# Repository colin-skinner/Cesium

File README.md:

# Cesium
Library for all code related to development of my home server and space projects. 

The main goal of this project is not simply to learn, but to focus on following through and finishing each sprint. Additionally, with working prototypes and code, I plan to use my designs to help aspiring engineers who want to develop these skills as well (open-source, potentially?).

Each stage will act as a sort of version that had a fully working system. When I add changes that completely break a system, then I'll re-rev the design for a new version.

## Stage/Version 0 (Test Boards to get my footing)
* Rocket Project Test Rocket Backup Board (in case Avionics wants to fly another)
* ESP32 WROOM breakout with USB-UART communication, power circuit (3V3, 5V LDOs, Battery), and CAN Bus
* Breakout with sensors over I2C
* Breakout with sensors over SPI

## Stage/Version 1
The goal of this design is to create an assortment of avionics boards useful for ground testing of amateur rocketry or satellites using the CAN bus and various ADCs for data collection.

* ESP-32 Boards connected by CAN (for simplicity) 
  * CAN Transceiver - _MCP2562_ or _MCP2544FD_
* Boards designed to be small footprint and scaleable
    * Single function (i.e. Ducers, Load Cells, etc.)
* EGSE Board connects to server via D+/D- USB OTG (ESP32 S3 capability)
    * Future boards use _CP2102_ for USB-UART communication 
        * (ESP32 modules with ethernet do not have USB OTG)
* Telemetry
    * At this stage, unique codes for each telemetry
        * Based on CAN 11-bit arbitration ID for a maximum of 2048 different telemetries
    * EGSE board will act as the "router" between "support rack" and CAN bus boards
* List of Boards
    * Load Switches
        * FET switching, _INA180_ current sense, actuation feedback
        * Uses _ADS8688_ (optimized for single-ended signals)
    * Pressure Transducers
        * Uses _ADS8688_ (optimized for single-ended signals)
    * Load Cells
        * Uses _ADS1256_ (optimized for diffrential signals)
    * Flight Computer
        * SPI communication with IMU, GPS, and Altimeter  
    * Recovery board
        * Powering, arming, and receiving data from spare [Stratologger CF](http://www.perfectflite.com/SLCF.html) altimeter from my freshman year rocket class
    * EGSE/Power board
        * Routes CAN packets over USB to "support rack"
        * Commands from Python commander are sent to CAN bus
        
* GSE functionality (Python)
    * Commander (PyComm)
    * Telemetry visualization (Telem)

## Stage 2+
* ESP32 boards with wired Ethernet
    * PHY - _LAN8720AI_
    * Potential onboard switch - _KSZ8567S_
    * Separate VLAN to differentiate boards from home network
* Radio board for wireless communication
* Fully realize a proper home server/network diagram and organization
    * Firewall, different VLANs for things
    * Plex media server
    * My own local version of services called S-Suite (after G-Suite)
* GSE functionality (Python)
    * Real time DAQ (FizzVizz)
    * MySQL Integration for data storage
* Other software
    * Scheduler 
    * State Machine

## Other future ideas
* IOT Home Automation 
* Connecting my Octoprint 3D printers

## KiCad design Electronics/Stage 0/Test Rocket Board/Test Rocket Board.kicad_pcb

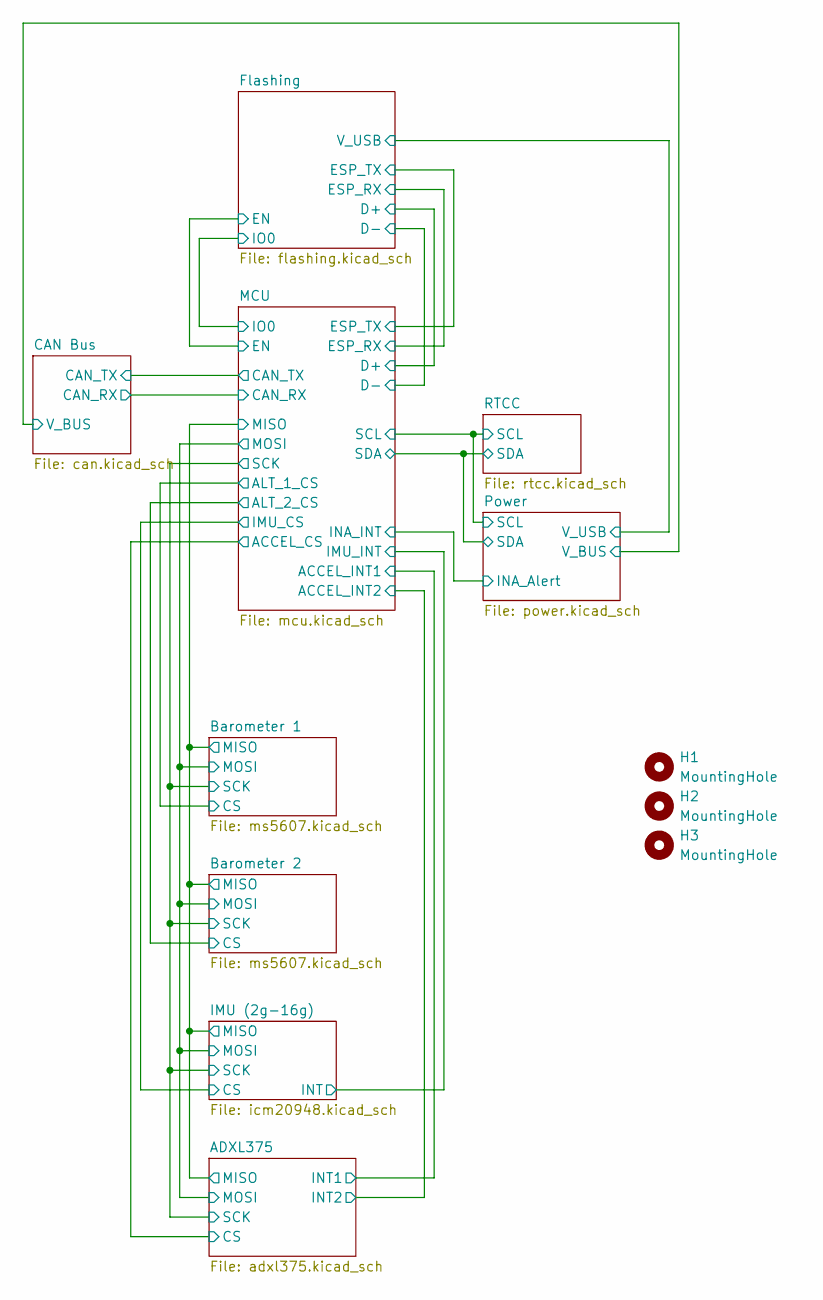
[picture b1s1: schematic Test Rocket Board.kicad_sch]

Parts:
H1, H2, H3: MountingHole; MountingHole_3.2mm_M3

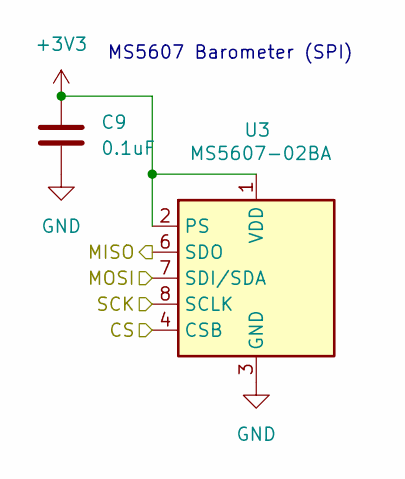
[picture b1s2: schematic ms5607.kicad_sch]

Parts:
C9: 0.1uF; C_0603_1608Metric
U3: MS5607-02BA; LGA-8_3x5mm_P1.25mm

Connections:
+3V3: C9.1, U3.1 (VDD), U3.2 (PS); also elsewhere on the board
/ADXL375/MISO: U3.6 (SDO); also elsewhere on the board
/ADXL375/MOSI: U3.7 (SDI/SDA); also elsewhere on the board
/ADXL375/SCK: U3.8 (SCLK); also elsewhere on the board
/Barometer 1/CS: U3.4 (CSB), U3.5 (CSB); also elsewhere on the board
GND: C9.2, U3.3 (GND); also elsewhere on the board

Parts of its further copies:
C10: 0.1uF; C_0603_1608Metric
U4: MS5607-02BA; LGA-8_3x5mm_P1.25mm

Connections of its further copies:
+3V3: C10.1, U4.1 (VDD), U4.2 (PS); also elsewhere on the board
/ADXL375/MISO: U4.6 (SDO); also elsewhere on the board
/ADXL375/MOSI: U4.7 (SDI/SDA); also elsewhere on the board
/ADXL375/SCK: U4.8 (SCLK); also elsewhere on the board
/Barometer 2/CS: U4.4 (CSB), U4.5 (CSB); also elsewhere on the board
GND: C10.2, U4.3 (GND); also elsewhere on the board

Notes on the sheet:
MS5607 Barometer (SPI)

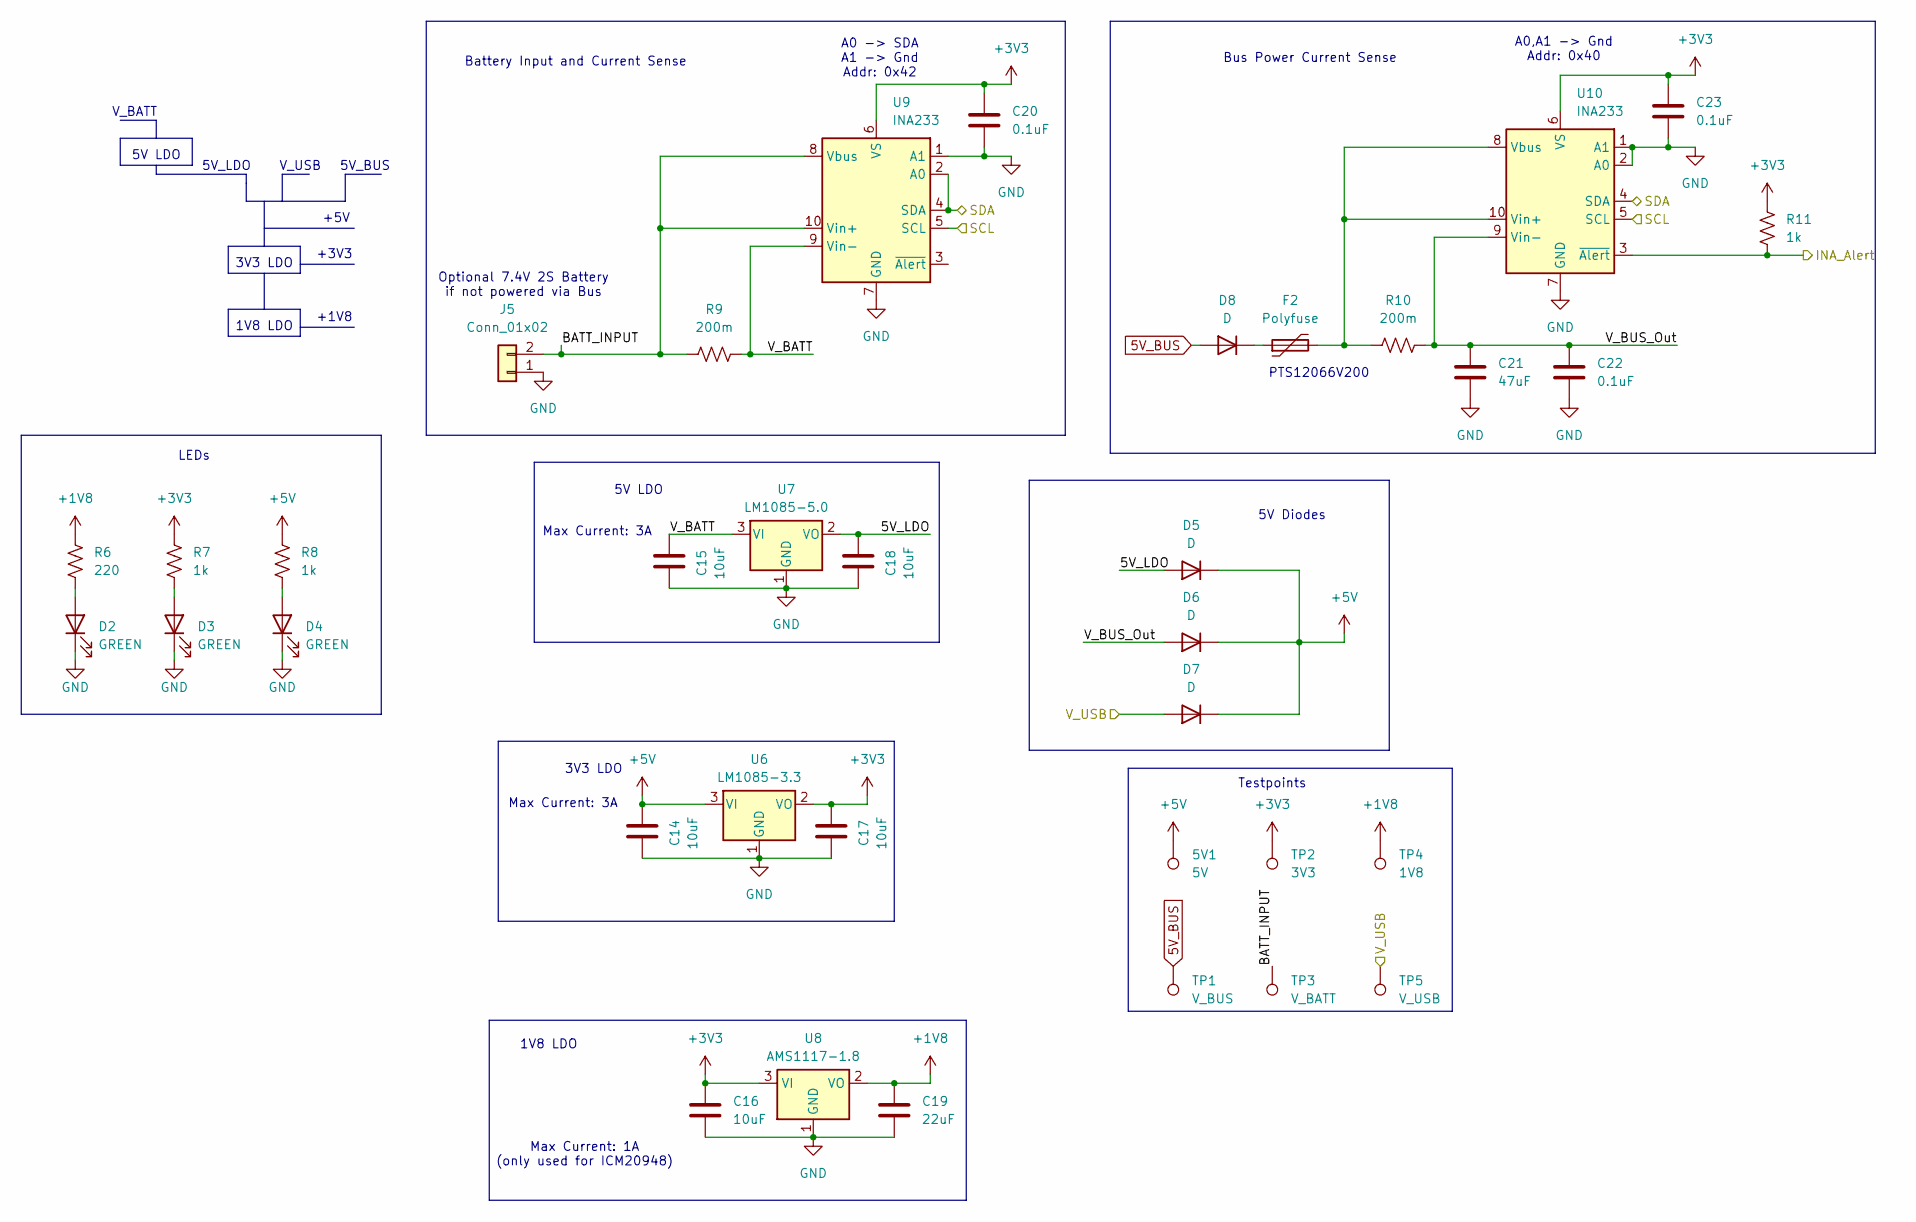
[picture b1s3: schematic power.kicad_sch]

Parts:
5V1: 5V; PinHeader_1x01_P2.54mm_Vertical
C14, C15, C16, C17, C18: 10uF; C_0603_1608Metric
C19: 22uF; C_0603_1608Metric
C20, C22, C23: 0.1uF; C_0603_1608Metric
C21: 47uF; C_0603_1608Metric
D2, D3, D4: GREEN; LED_0603_1608Metric_Pad1.05x0.95mm_HandSolder
D5, D6, D7, D8: D; D_0603_1608Metric
F2: Polyfuse; Fuse_1206_3216Metric
J5: Conn_01x02; AMASS_XT60-M_1x02_P7.20mm_Vertical
R6: 220; R_0603_1608Metric
R7, R8, R11: 1k; R_0603_1608Metric
R9, R10: 200m; R_0603_1608Metric
TP1: V_BUS; PinHeader_1x01_P2.54mm_Vertical
TP2: 3V3; PinHeader_1x01_P2.54mm_Vertical
TP3: V_BATT; PinHeader_1x01_P2.54mm_Vertical
TP4: 1V8; PinHeader_1x01_P2.54mm_Vertical
TP5: V_USB; PinHeader_1x01_P2.54mm_Vertical
U6: LM1085-3.3; TO-263-3_TabPin2
U7: LM1085-5.0; TO-263-3_TabPin2
U8: AMS1117-1.8; SOT-223-3_TabPin2
U9, U10: INA233; VSSOP-10_3x3mm_P0.5mm

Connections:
5V_BUS: D8.2 (A), TP1.1; also elsewhere on the board
+1V8: C19.1, R6.2, TP4.1, U8.2 (VO); also elsewhere on the board
+3V3: C16.1, C17.2, C20.1, C23.1, R7.2, R11.2, TP2.1, U6.2 (VO), U8.3 (VI), U9.6 (VS), U10.6 (VS); also elsewhere on the board
+5V: 5V1.1, C14.2, D5.1 (K), D6.1 (K), D7.1 (K), R8.2, U6.3 (VI); also elsewhere on the board
/Flashing/V_USB: D7.2 (A), TP5.1; also elsewhere on the board
/MCU/INA_INT: R11.1, U10.3 (~Alert); also elsewhere on the board
/MCU/SCL: U9.5 (SCL), U10.5 (SCL); also elsewhere on the board
/MCU/SDA: U9.2 (A0), U9.4 (SDA), U10.4 (SDA); also elsewhere on the board
/Power/5V_LDO: C18.2, D5.2 (A), U7.2 (VO)
/Power/BATT_INPUT: J5.2, R9.1, TP3.1, U9.8 (Vbus), U9.10 (Vin+)
/Power/V_BATT: C15.2, R9.2, U7.3 (VI), U9.9 (Vin-)
/Power/V_BUS_Out: C21.1, C22.1, D6.2 (A), R10.2, U10.9 (Vin-)
GND: C14.1, C15.1, C16.2, C17.1, C18.1, C19.2, C20.2, C21.2, C22.2, C23.2, D2.1 (K), D3.1 (K), D4.1 (K), J5.1, U6.1 (GND), U7.1 (GND), U8.1 (GND), U9.1 (A1), U9.7 (GND), U10.1 (A1), U10.2 (A0), U10.7 (GND); also elsewhere on the board
unnamed: D2.2 (A), R6.1
unnamed: D3.2 (A), R7.1
unnamed: D4.2 (A), R8.1
unnamed: D8.1 (K), F2.1
unnamed: F2.2, R10.1, U10.8 (Vbus), U10.10 (Vin+)

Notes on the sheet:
Battery Input and Current Sense
Testpoints
PTS12066V200
5V LDO
Max Current: 3A
LEDs
3V3 LDO
+3V3
Max Current: 1A (only used for ICM20948)
5V_LDO
1V8 LDO
Bus Power Current Sense
A0 -> SDA A1 -> Gnd Addr: 0x42
+1V8
+5V
5V_BUS
V_USB
Optional 7.4V 2S Battery if not powered via Bus
V_BATT
5V Diodes
A0,A1 -> Gnd Addr: 0x40

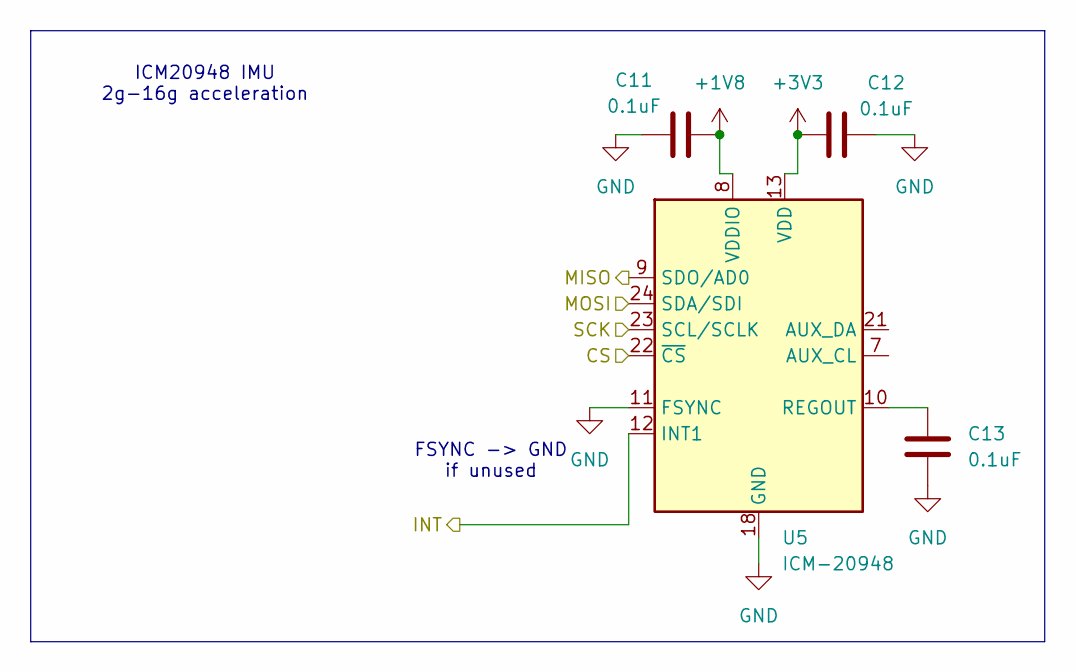
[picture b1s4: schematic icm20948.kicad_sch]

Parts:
C11, C12, C13: 0.1uF; C_0603_1608Metric
U5: ICM-20948; InvenSense_QFN-24_3x3mm_P0.4mm

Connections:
+1V8: C11.2, U5.8 (VDDIO); also elsewhere on the board
+3V3: C12.1, U5.13 (VDD); also elsewhere on the board
/ADXL375/MISO: U5.9 (SDO/AD0); also elsewhere on the board
/ADXL375/MOSI: U5.24 (SDA/SDI); also elsewhere on the board
/ADXL375/SCK: U5.23 (SCL/SCLK); also elsewhere on the board
/IMU (2g-16g)/CS: U5.22 (~CS); also elsewhere on the board
/IMU (2g-16g)/INT: U5.12 (INT1); also elsewhere on the board
GND: C11.1, C12.2, C13.2, U5.11 (FSYNC), U5.18 (GND), U5.20 (GND); also elsewhere on the board
unnamed: C13.1, U5.10 (REGOUT)

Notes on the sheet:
ICM20948 IMU 2g-16g acceleration
FSYNC -> GND if unused

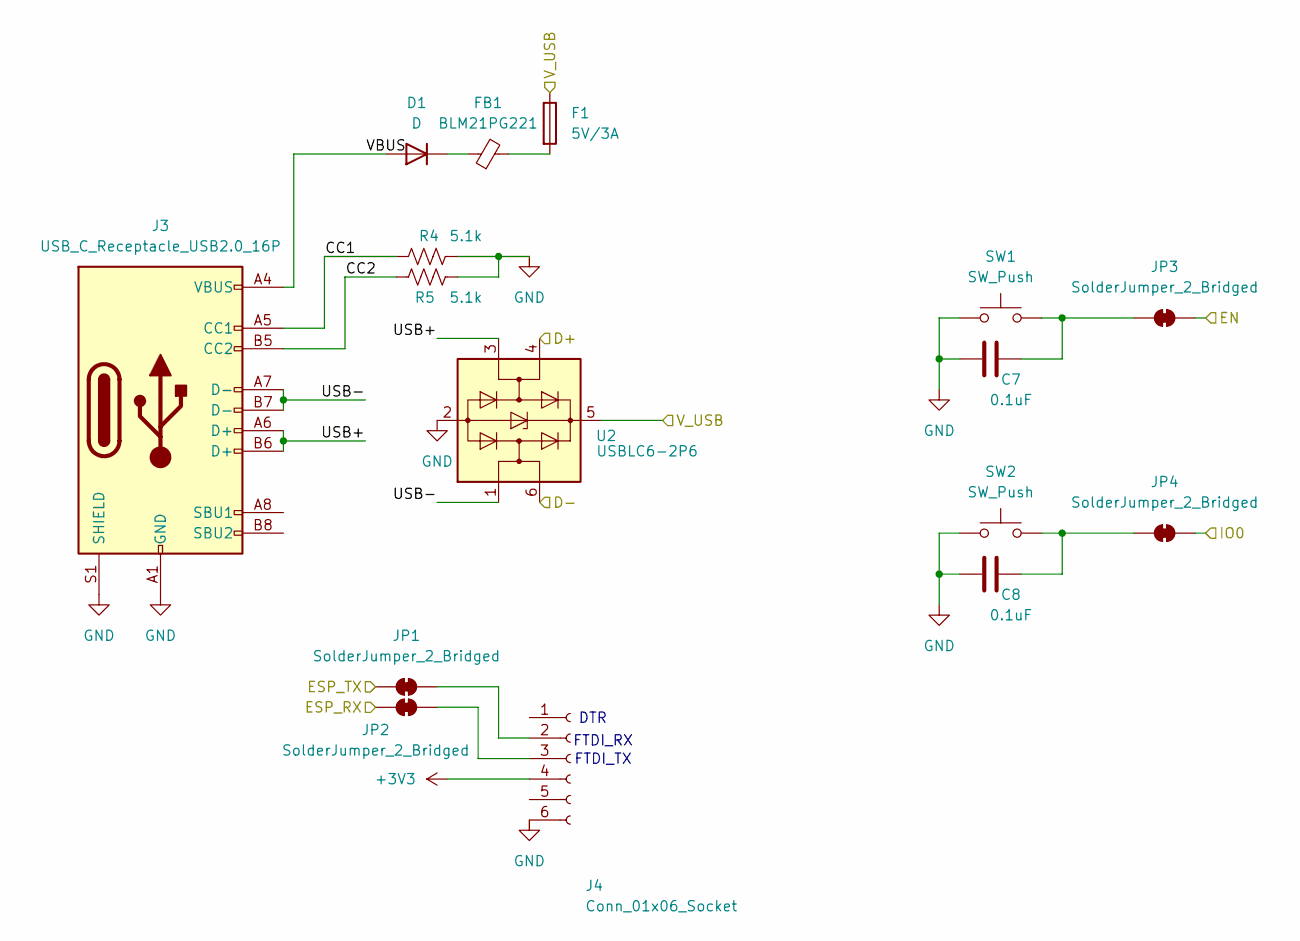
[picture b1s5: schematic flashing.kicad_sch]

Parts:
C7, C8: 0.1uF; C_0603_1608Metric
D1: D; D_0603_1608Metric
F1: 5V/3A; Fuse_0603_1608Metric
FB1: BLM21PG221; L_0603_1608Metric_Pad1.05x0.95mm_HandSolder
J3: USB_C_Receptacle_USB2.0_16P; USB_C_Receptacle_HRO_TYPE-C-31-M-12
J4: Conn_01x06_Socket; PinHeader_1x06_P2.54mm_Vertical
JP1, JP2, JP3, JP4: SolderJumper_2_Bridged; SolderJumper-2_P1.3mm_Bridged_Pad1.0x1.5mm
R4, R5: 5.1k; R_0603_1608Metric
SW1, SW2: SW_Push; SW_SPST_EVPBF
U2: USBLC6-2P6; SOT-666

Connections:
+3V3: J4.4; also elsewhere on the board
/Flashing/CC1: J3.A5 (CC1), R4.1
/Flashing/CC2: J3.B5 (CC2), R5.1
/Flashing/D+: U2.4 (I/O2); also elsewhere on the board
/Flashing/D-: U2.6 (I/O1); also elsewhere on the board
/Flashing/EN: JP3.2 (B); also elsewhere on the board
/Flashing/ESP_RX: JP2.2 (B); also elsewhere on the board
/Flashing/ESP_TX: JP1.1 (A); also elsewhere on the board
/Flashing/IO0: JP4.2 (B); also elsewhere on the board
/Flashing/USB+: J3.A6 (D+), J3.B6 (D+), U2.3 (I/O2)
/Flashing/USB-: J3.A7 (D-), J3.B7 (D-), U2.1 (I/O1)
/Flashing/VBUS: D1.2 (A), J3.A4 (VBUS), J3.A9 (VBUS), J3.B4 (VBUS), J3.B9 (VBUS)
/Flashing/V_USB: F1.1, U2.5 (VBUS); also elsewhere on the board
GND: C7.1, C8.1, J3.A1 (GND), J3.A12 (GND), J3.B1 (GND), J3.B12 (GND), J3.S1 (SHIELD), J4.6, R4.2, R5.2, SW1.1, SW2.1, U2.2 (GND); also elsewhere on the board
unnamed: D1.1 (K), FB1.1
unnamed: F1.2, FB1.2
unnamed: J4.2, JP1.2 (B)
unnamed: J4.3, JP2.1 (A)
unnamed: C7.2, JP3.1 (A), SW1.2
unnamed: C8.2, JP4.1 (A), SW2.2

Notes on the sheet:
DTR
FTDI_RX
FTDI_TX

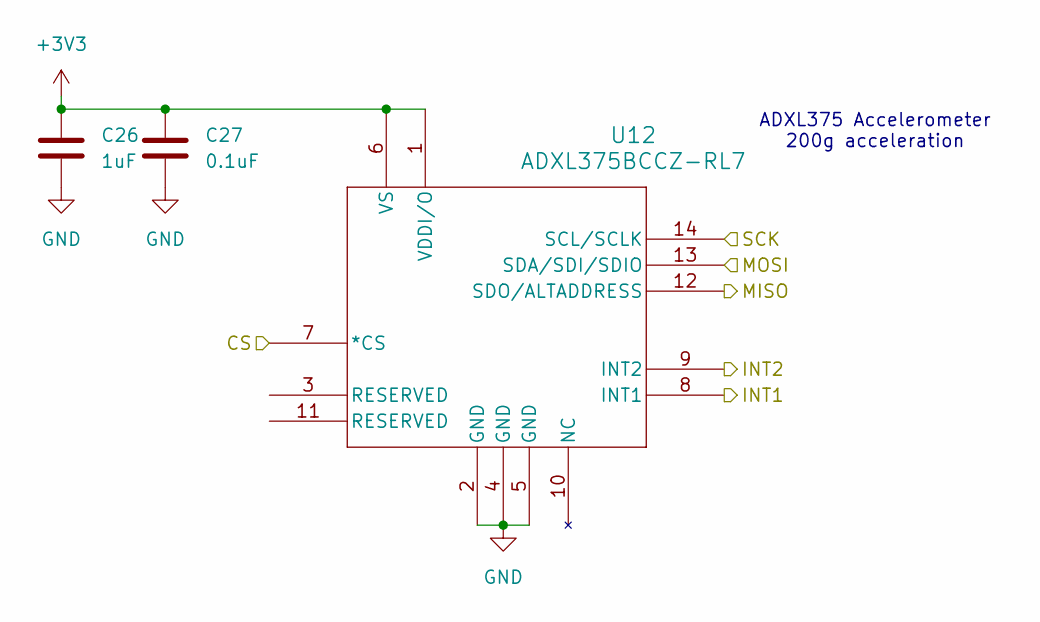
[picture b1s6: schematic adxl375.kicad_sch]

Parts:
C26: 1uF; C_0603_1608Metric
C27: 0.1uF; C_0603_1608Metric
U12: ADXL375BCCZ-RL7; LGA_CC-14-1_ADI

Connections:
+3V3: C26.1, C27.1, U12.1 (VDDI/O), U12.6 (VS); also elsewhere on the board
/ADXL375/CS: U12.7 (*CS); also elsewhere on the board
/ADXL375/INT1: U12.8 (INT1); also elsewhere on the board
/ADXL375/INT2: U12.9 (INT2); also elsewhere on the board
/ADXL375/MISO: U12.12 (SDO/ALTADDRESS); also elsewhere on the board
/ADXL375/MOSI: U12.13 (SDA/SDI/SDIO); also elsewhere on the board
/ADXL375/SCK: U12.14 (SCL/SCLK); also elsewhere on the board
GND: C26.2, C27.2, U12.2 (GND), U12.4 (GND), U12.5 (GND); also elsewhere on the board

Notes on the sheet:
ADXL375 Accelerometer 200g acceleration

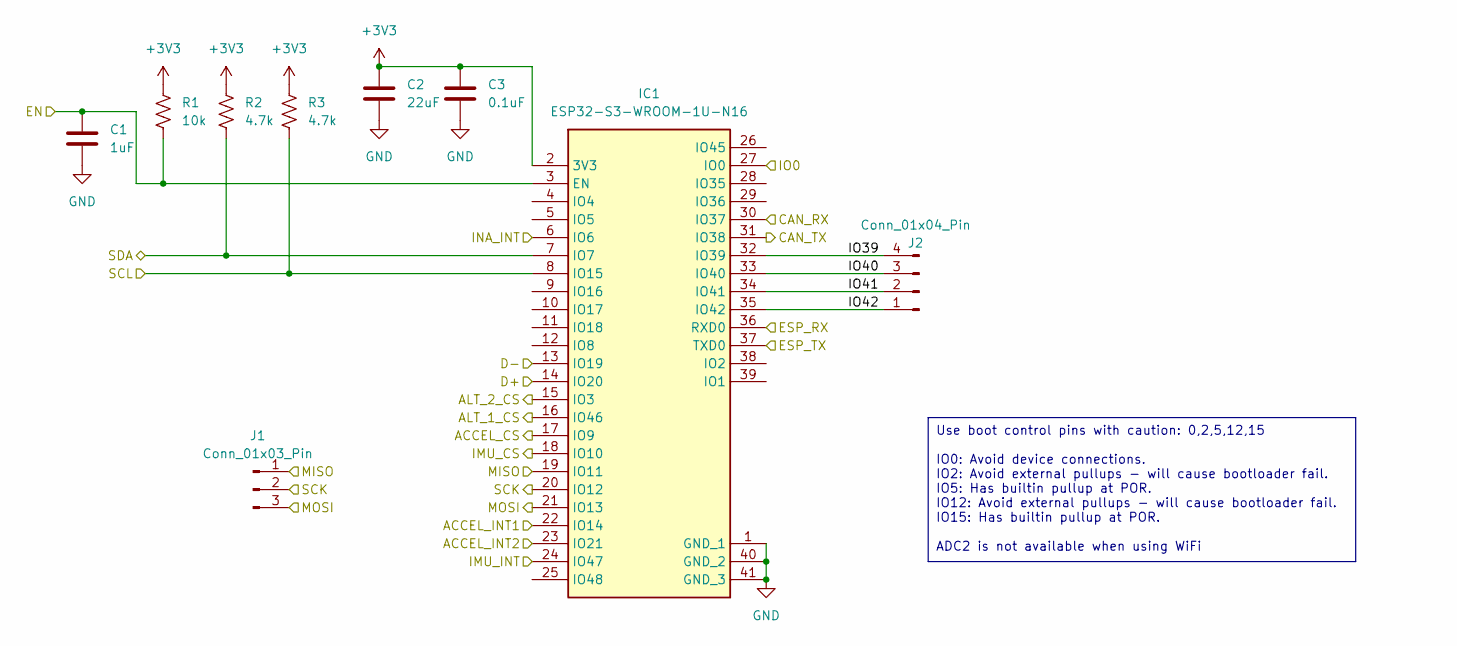
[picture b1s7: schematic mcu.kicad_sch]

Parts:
C1: 1uF; C_0603_1608Metric
C2: 22uF; C_0603_1608Metric
C3: 0.1uF; C_0603_1608Metric
IC1: ESP32-S3-WROOM-1U-N16; ESP32-S3-WROOM-1U; Mouser Part Number 356-ESP32S3WROM1UN16
J1: Conn_01x03_Pin; PinHeader_1x03_P2.54mm_Vertical
J2: Conn_01x04_Pin; PinHeader_1x04_P2.54mm_Vertical
R1: 10k; R_0603_1608Metric
R2, R3: 4.7k; R_0603_1608Metric

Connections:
+3V3: C2.2, C3.2, IC1.2 (3V3), R1.1, R2.1, R3.1; also elsewhere on the board
/ADXL375/CS: IC1.17 (IO9); also elsewhere on the board
/ADXL375/INT1: IC1.22 (IO14); also elsewhere on the board
/ADXL375/INT2: IC1.23 (IO21); also elsewhere on the board
/ADXL375/MISO: IC1.19 (IO11), J1.1; also elsewhere on the board
/ADXL375/MOSI: IC1.21 (IO13), J1.3; also elsewhere on the board
/ADXL375/SCK: IC1.20 (IO12), J1.2; also elsewhere on the board
/Barometer 1/CS: IC1.16 (IO46); also elsewhere on the board
/Barometer 2/CS: IC1.15 (IO3); also elsewhere on the board
/CAN Bus/CAN_RX: IC1.30 (IO37); also elsewhere on the board
/CAN Bus/CAN_TX: IC1.31 (IO38); also elsewhere on the board
/Flashing/D+: IC1.14 (IO20); also elsewhere on the board
/Flashing/D-: IC1.13 (IO19); also elsewhere on the board
/Flashing/EN: C1.2, IC1.3 (EN), R1.2; also elsewhere on the board
/Flashing/ESP_RX: IC1.36 (RXD0); also elsewhere on the board
/Flashing/ESP_TX: IC1.37 (TXD0); also elsewhere on the board
/Flashing/IO0: IC1.27 (IO0); also elsewhere on the board
/IMU (2g-16g)/CS: IC1.18 (IO10); also elsewhere on the board
/IMU (2g-16g)/INT: IC1.24 (IO47); also elsewhere on the board
/MCU/INA_INT: IC1.6 (IO6); also elsewhere on the board
/MCU/IO39: IC1.32 (IO39), J2.4
/MCU/IO40: IC1.33 (IO40), J2.3
/MCU/IO41: IC1.34 (IO41), J2.2
/MCU/IO42: IC1.35 (IO42), J2.1
/MCU/SCL: IC1.8 (IO15), R3.2; also elsewhere on the board
/MCU/SDA: IC1.7 (IO7), R2.2; also elsewhere on the board
GND: C1.1, C2.1, C3.1, IC1.1 (GND_1), IC1.40 (GND_2), IC1.41 (GND_3); also elsewhere on the board

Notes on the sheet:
Use boot control pins with caution: 0,2,5,12,15 IO0: Avoid device connections. IO2: Avoid external pullups - will cause bootloader fail. IO5: Has builtin pullup at POR. IO12: Avoid external pullups - will cause bootloader fail. IO15: Has builtin pullup at POR. ADC2 is not available when using WiFi

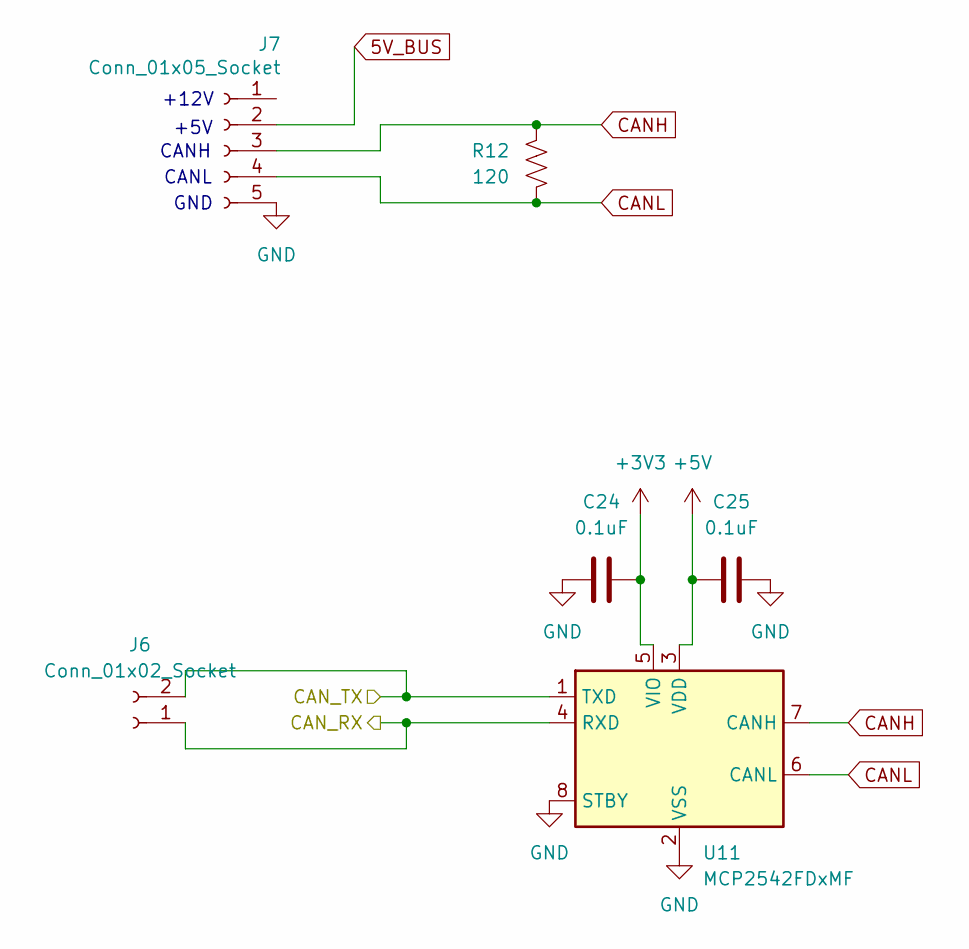
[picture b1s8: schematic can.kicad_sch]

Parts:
C24, C25: 0.1uF; C_0603_1608Metric
J6: Conn_01x02_Socket; PinHeader_1x02_P2.54mm_Vertical
J7: Conn_01x05_Socket; PinHeader_1x05_P2.54mm_Vertical
R12: 120; R_0603_1608Metric
U11: MCP2542FDxMF; DFN-8-1EP_3x3mm_P0.65mm_EP1.55x2.4mm

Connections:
5V_BUS: J7.2; also elsewhere on the board
+3V3: C24.2, U11.5 (VIO); also elsewhere on the board
+5V: C25.1, U11.3 (VDD); also elsewhere on the board
/CAN Bus/CAN_RX: J6.1, U11.4 (RXD); also elsewhere on the board
/CAN Bus/CAN_TX: J6.2, U11.1 (TXD); also elsewhere on the board
CANH: J7.3, R12.1, U11.7 (CANH)
CANL: J7.4, R12.2, U11.6 (CANL)
GND: C24.1, C25.2, J7.5, U11.2 (VSS), U11.8 (STBY), U11.9 (VSS); also elsewhere on the board

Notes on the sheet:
CANH
+5V
+12V
GND
CANL

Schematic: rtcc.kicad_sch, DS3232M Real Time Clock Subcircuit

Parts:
BT1: BAT-HLD-012-THM; BAT_BAT-HLD-012-THM
C4, C6: 0.1uF; C_0603_1608Metric
C5: 1uF; C_0603_1608Metric
U1: DS3232M; SOIC-8_3.9x4.9mm_P1.27mm

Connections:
+3V3: C5.1, C6.1, U1.2 (VCC); also elsewhere on the board
/MCU/SCL: U1.8 (SCL); also elsewhere on the board
/MCU/SDA: U1.7 (SDA); also elsewhere on the board
GND: BT1.N, C4.1, C5.2, C6.2, U1.5 (GND); also elsewhere on the board
unnamed: BT1.P1, C4.2, U1.6 (VBAT)

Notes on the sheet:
2.5µA timekeeping current -> 14,000 Hours
3V Backup Battery CR1220 (35 mAh)

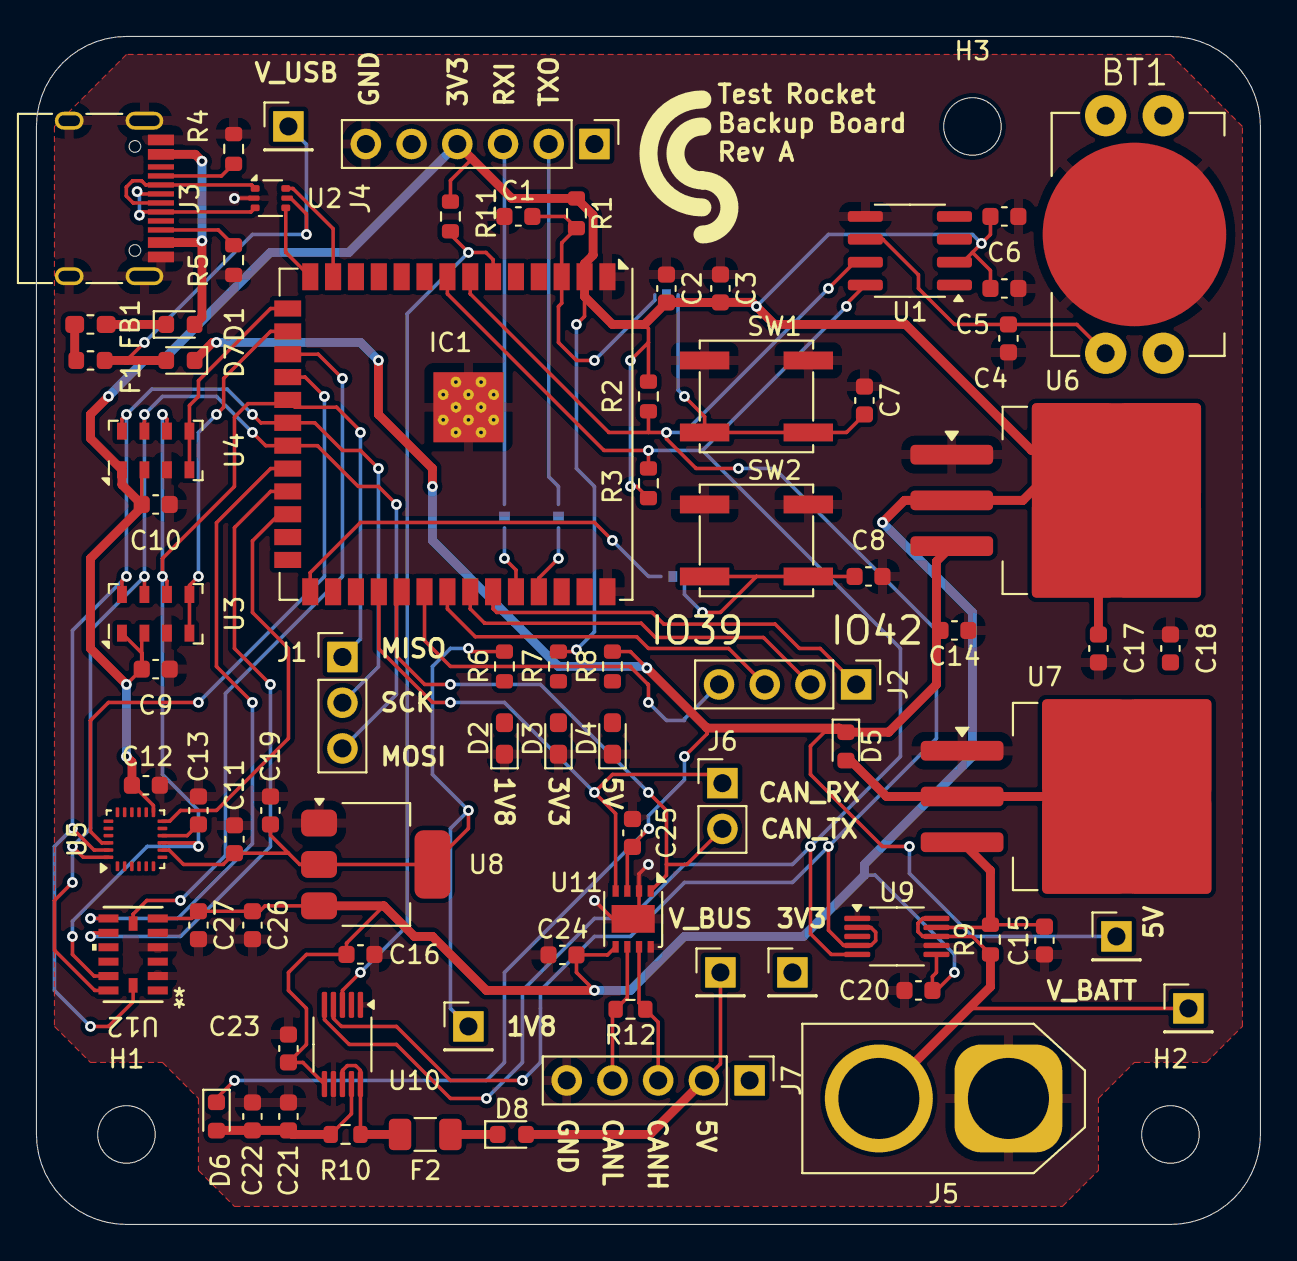
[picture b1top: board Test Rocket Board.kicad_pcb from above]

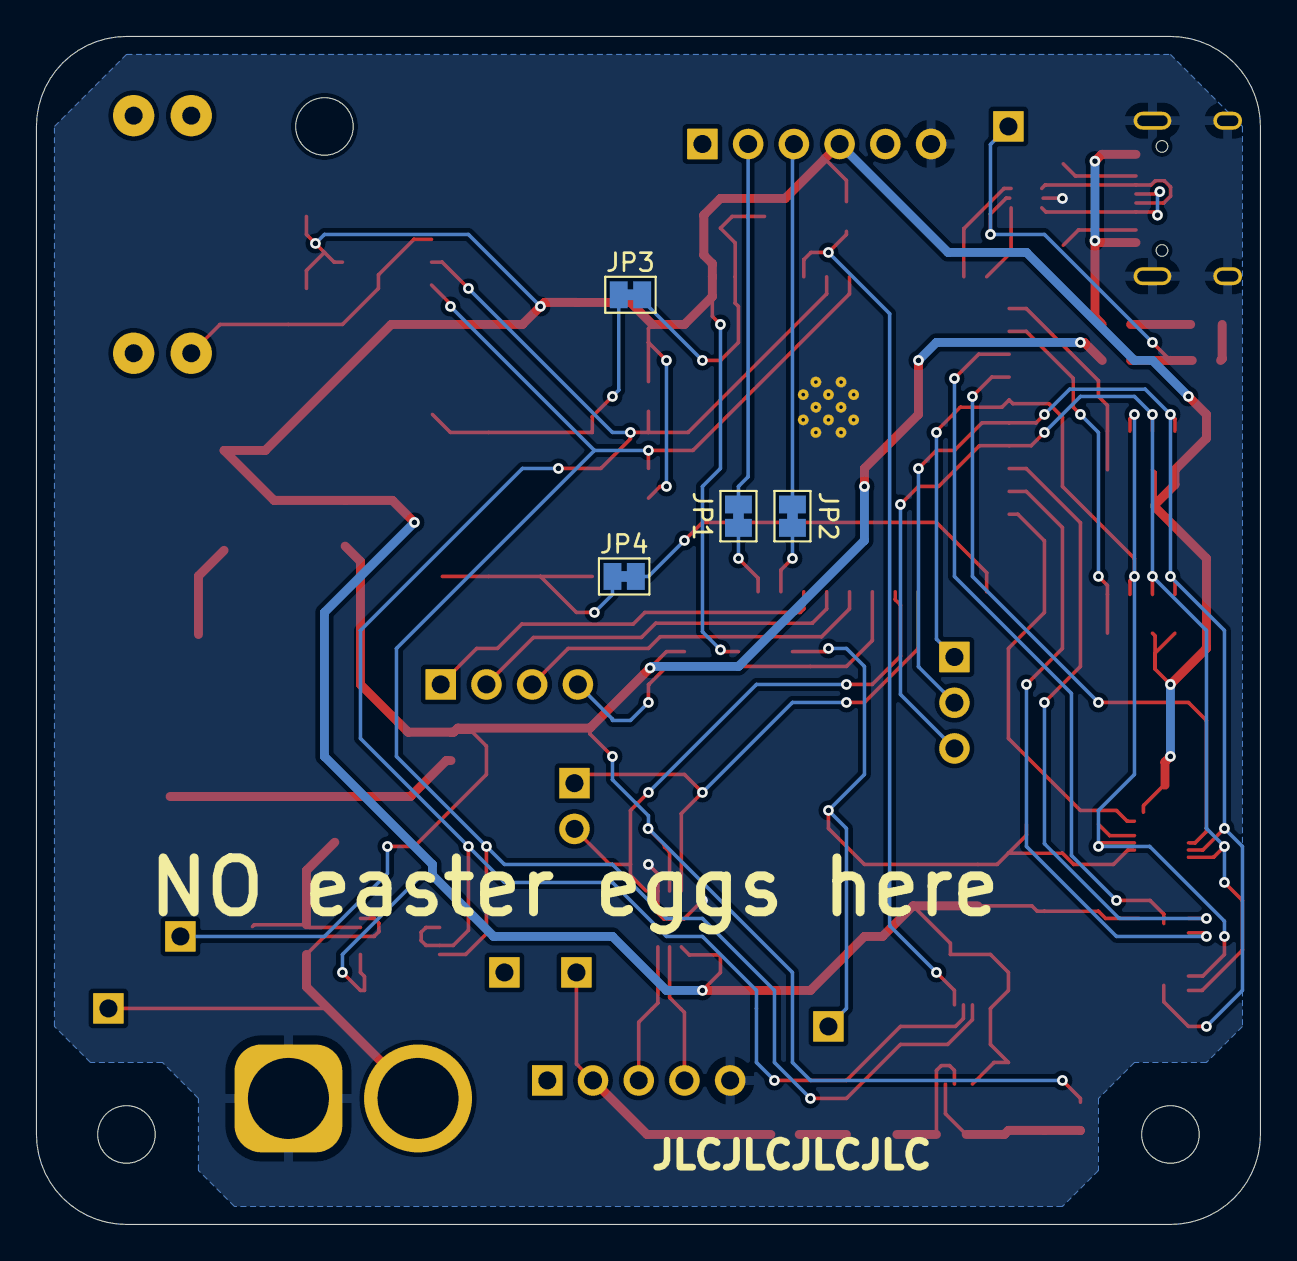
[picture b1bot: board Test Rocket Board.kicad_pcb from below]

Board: 2 copper layers, 68.0 x 66.0 mm, 86 parts (4 on the bottom side), 55 nets.

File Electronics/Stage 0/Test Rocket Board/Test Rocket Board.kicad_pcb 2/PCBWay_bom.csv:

Designator,Quantity,Value,Footprint,Package,MPN,DNP,Mount_Type,Description,SnapEDA_Link,Check_prices,Price,MF,MP,Purchase-URL,Availability,Description_1,Sim.Device,Sim.Pins,Height,Mouser Part Number,Mouser Price/Stock,Manufacturer_Name
5V1,1,5V,PinHeader_1x01_P2.54mm_Vertical,,,,tht,test point,,,,,,,,,,,,,,
BT1,1,BAT-HLD-012-THM,BAT_BAT-HLD-012-THM,None,,,tht,,https://www.snapeda.com/parts/BAT-HLD-012-THM/Linx+Technolog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,https://www.snapeda.com/parts/BAT-HLD-012-THM/Linx+Technolog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,None,Linx Technologies,BAT-HLD-012-THM,https://www.snapeda.com/api/url_track_click_mouser/?unipart_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 Technologies&part_name=BAT-HLD-012-THM&search_term=None,In Stock,"Holder for CR1216 and CR1225 Batteries, Through-Hole Mount, Bulk Packaging",,,,,,
"C1, C26, C5",3,1uF,C_0603_1608Metric,,,,smt,Unpolarized capacitor,,,,,,,,,,,,,,
"C10, C11, C12, C13, C20, C22, C23, C24, C25, C27, C3, C4, C6, C7, C8, C9",16,0.1uF,C_0603_1608Metric,,,,smt,Unpolarized capacitor,,,,,,,,,,,,,,
"C14, C15, C16, C17, C18",5,10uF,C_0603_1608Metric,,,,smt,Unpolarized capacitor,,,,,,,,,,,,,,
"C19, C2",2,22uF,C_0603_1608Metric,,,,smt,Unpolarized capacitor,,,,,,,,,,,,,,
C21,1,47uF,C_0603_1608Metric,,,,smt,Unpolarized capacitor,,,,,,,,,,,,,,
"D1, D5, D6, D7, D8",5,D,D_0603_1608Metric,,,,smt,Diode,,,,,,,,,D,1=K 2=A,,,,
"D2, D3, D4",3,GREEN,LED_0603_1608Metric_Pad1.05x0.95mm_HandSolder,,,,smt,,,,,,,,,,,,,,,
F1,1,5V/3A,Fuse_0603_1608Metric,,,,smt,Fuse,,,,,,,,,,,,,,
F2,1,Polyfuse,Fuse_1206_3216Metric,,,,smt,"Resettable fuse, polymeric positive temperature coefficient",,,,,,,,,,,,,,
FB1,1,BLM21PG221,L_0603_1608Metric_Pad1.05x0.95mm_HandSolder,,,,smt,,,,,,,,,,,,,,,
IC1,1,ESP32-S3-WROOM-1U-N16,ESP32-S3-WROOM-1U,,ESP32-S3-WROOM-1U-N16,,smt,"Multiprotocol Modules SMD Module, ESP32-S3, 16 MB SPI Flash, IPEX Antenna Connector",,,,,,,,,,,3.35,356-ESP32S3WROM1UN16,https://www.mouser.co.uk/ProductDetail/Espressif-Systems/ESP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,Espressif Systems
J1,1,Conn_01x03_Pin,PinHeader_1x03_P2.54mm_Vertical,,,,tht,"Generic connector, single row, 01x03, script generated",,,,,,,,,,,,,,
J2,1,Conn_01x04_Pin,PinHeader_1x04_P2.54mm_Vertical,,,,tht,"Generic connector, single row, 01x04, script generated",,,,,,,,,,,,,,
J3,1,USB_C_Receptacle_USB2.0_16P,USB_C_Receptacle_HRO_TYPE-C-31-M-12,,,,smt,USB 2.0-only 16P Type-C Receptacle connector,,,,,,,,,,,,,,
J4,1,Conn_01x06_Socket,PinHeader_1x06_P2.54mm_Vertical,,,,tht,"Generic connector, single row, 01x06, script generated",,,,,,,,,,,,,,
J5,1,Conn_01x02,AMASS_XT60-M_1x02_P7.20mm_Vertical,,,,tht,"Generic connector, single row, 01x02, script generated (kicad-library-utils/schlib/autogen/connector/)",,,,,,,,,,,,,,
J6,1,Conn_01x02_Socket,PinHeader_1x02_P2.54mm_Vertical,,,,tht,"Generic connector, single row, 01x02, script generated",,,,,,,,,,,,,,
J7,1,Conn_01x05_Socket,PinHeader_1x05_P2.54mm_Vertical,,,,tht,"Generic connector, single row, 01x05, script generated",,,,,,,,,,,,,,
R1,1,10k,R_0603_1608Metric,,,,smt,"Resistor, US symbol",,,,,,,,,,,,,,
"R10, R9",2,200m,R_0603_1608Metric,,,,smt,"Resistor, US symbol",,,,,,,,,,,,,,
"R11, R7, R8",3,1k,R_0603_1608Metric,,,,smt,"Resistor, US symbol",,,,,,,,,,,,,,
R12,1,120,R_0603_1608Metric,,,,smt,"Resistor, US symbol",,,,,,,,,,,,,,
"R2, R3",2,4.7k,R_0603_1608Metric,,,,smt,"Resistor, US symbol",,,,,,,,,,,,,,
"R4, R5",2,5.1k,R_0603_1608Metric,,,,smt,"Resistor, US symbol",,,,,,,,,,,,,,
R6,1,220,R_0603_1608Metric,,,,smt,"Resistor, US symbol",,,,,,,,,,,,,,
"SW1, SW2",2,SW_Push,SW_SPST_EVPBF,,,,smt,"Push button switch, generic, two pins",,,,,,,,,,,,,,
TP1,1,V_BUS,PinHeader_1x01_P2.54mm_Vertical,,,,tht,test point,,,,,,,,,,,,,,
TP2,1,3V3,PinHeader_1x01_P2.54mm_Vertical,,,,tht,test point,,,,,,,,,,,,,,
TP3,1,V_BATT,PinHeader_1x01_P2.54mm_Vertical,,,,tht,test point,,,,,,,,,,,,,,
TP4,1,1V8,PinHeader_1x01_P2.54mm_Vertical,,,,tht,test point,,,,,,,,,,,,,,
TP5,1,V_USB,PinHeader_1x01_P2.54mm_Vertical,,,,tht,test point,,,,,,,,,,,,,,
U1,1,DS3232M,SOIC-8_3.9x4.9mm_P1.27mm,,,,smt,"±5ppm, I2C Real-Time Clock with SRAM SOIC-8",,,,,,,,,,,,,,
"U10, U9",2,INA233,VSSOP-10_3x3mm_P0.5mm,,,,smt,"High-Side or Low-Side Measurement, Bi-Directional Current and Power Monitor (0-36V) with I2C, SMBus-, and PMBus-Compatible Interface, VSSOP-10",,,,,,,,,,,,,,
U11,1,MCP2542FDxMF,DFN-8-1EP_3x3mm_P0.65mm_EP1.55x2.4mm,,,,smt,"CAN-FD Transceiver, Wake-Up on CAN activity, 8Mbps, 5V supply, STBY pin, 3x3 DFN-8",,,,,,,,,,,,,,
U12,1,ADXL375BCCZ-RL7,LGA_CC-14-1_ADI,,,,smt,,,,,,,,,,,,,,,
U2,1,USBLC6-2P6,SOT-666,,,,smt,,,,,,,,,,,,,,,
"U3, U4",2,MS5607-02BA,LGA-8_3x5mm_P1.25mm,,,,smt,"Barometric pressure sensor, 20cm resolution, 10 to 1200 mbar, I2C and SPI interface up to 20MHz, LGA-8",,,,,,,,,,,,,,
U5,1,ICM-20948,InvenSense_QFN-24_3x3mm_P0.4mm,,,,smt,"InvenSense 9-Axis Motion Sensor, Accelerometer, Gyroscope, Compass, I2C/SPI, QFN-24",,,,,,,,,,,,,,
U6,1,LM1085-3.3,TO-263-3_TabPin2,,,,smt,"3A 27V Linear Regulator, Fixed Output 3.3V, TO-220/TO-263",,,,,,,,,,,,,,
U7,1,LM1085-5.0,TO-263-3_TabPin2,,,,smt,"3A 25V Linear Regulator, Fixed Output 5.0V, TO-220/TO-263",,,,,,,,,,,,,,
U8,1,AMS1117-1.8,SOT-223-3_TabPin2,,,,smt,"1A Low Dropout regulator, positive, 1.8V fixed output, SOT-223",,,,,,,,,,,,,,
